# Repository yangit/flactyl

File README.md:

# Flactyl

## Contacts

If you need help building this keyboard or have any questions you can drop me a line at [yan@yan.my](mailto:yan@yan.my)

I'd be happy to help!

## Release notes

### 5.1

- Fix routes too close to mounting screw holes can be stripped if screw is overtightened

### 5.0

- PCBs v4 are not compatible with case v5, connector cutout location have been changed
- Moved thumb JST connector so that it is not necessary to trim JST cable
- Moved JST connectors, reset button, power switch on main PCBs such that it it easier make parametric case
- Added `.scad` for Iceberg/Clay cases

### 4.2

- First public release

## Features

- Thumb cluster with 6 keys, easy to use in combos, so ~12 combinations depending on how you setup combos
- 15g SPRiT springs to make same finger combos super easy
- Thumb cluster keys are designed to be poked with thumb nail/nose, not pressed with soft area, allows for easy access to all 6 keys with no wrist movement
- Multiple cases including the `clay` case to easily prototype your thumb cluster location
- Low distance between pinky and the table, allows to rest palms directly on the table without floating them, or using wrist rests.
- Heavy tenting at 60 degrees
- Kailh Choc V1 hotswap, with choc spacing
- Rotary encoder
- Ergogen for PCB with some custom scripts to generate `.bom` `.pos` files for jlcpcb.com SMT assembly service, and output outlines for easier 3d case designing
- zmk-config generator with custom NodeJS script to make layer declaration easier and more readable
- Nice!Nano positioned right under the keys, hiding itself, without need for manual wiring (because of that PCBs are non reversible)
- Can fit huge batteries
- Magnetic stripe to securely fasten to the table

## Videos and links

- Youtube video with detailed review is [here](https://www.youtube.com/watch?v=Pdhb9uNnzU0)
- Short [typing video](https://www.youtube.com/watch?v=eU5eg4PKMlQ)
- 3d models can be [interactively rotated](https://yangit.github.io/flactyl/)
- Video how to order 3d case from JLCPCB.com [here](https://www.youtube.com/watch?v=07qFKaykjfg)
- Video how to order PCBs from JLCPCB.com [here](https://youtu.be/oP7d0jU99oc)
- Reddit [thread](https://www.reddit.com/r/ErgoMechKeyboards/comments/13qep4y/after_4_year_lurking_and_2_years_building_my_own/)
- You can find [basic](https://github.com/yangit/zmk-config-flactyl/) zmk-config for this board and [my own config generator](https://github.com/yangit/zmk-config/)
- It took me two years to finish this project, thanks to [KBD.news](https://kbd.news/) for inspiration!

## Cases

There are 3 cases available:
**Clay**, **Iceberg**, **Hitam**  
3d models can be [interactively rotated](https://yangit.github.io/flactyl/)

### Clay

Consist of two pieces, you are supposed to put clay/play dough in it and see what position is best for you. It is pretty usable already.

### Iceberg

Consists of single hollow box, switches are exposed on the sides.

### Hitam

Pretty involved shape to cover all the keys from the sides as well.

## Customize case

You can customize thumb cluster location reasonably easy using
`./scad/` folder. Try to play around with it, you need OpenScad free software. Look for `./scad/readme.md` for more details.

## Build

High-level build steps looks like so:

- Select which case you want to print
- Order case and PCB from JLCPCB or any other pcb/3d printing vendor
- Order parts online from various vendors according to the parts list
- Solder
  - Pins on the Nice!Nanos themselves see [this](https://docs.splitkb.com/hc/en-us/articles/360011263059-How-do-I-socket-a-microcontroller-) guide
  - Headers for Nice!Nanos on the left and right PCBs
  - Hot-swap connectors for switches on all PCBs
  - Two switches above Nice!Nanos on each side of PCB (letters G,T,J,U on QUERTY)
  - Rotary encoders to PCBs
  - Batteries with connectors (only for wireless build)
- Assemble (do not worry, if you got this far it is only pure joy left)
  - Small tip, when screwing everything, you should use 2 nuts per screw, it goes like so
  - SCREW, WASHER, PCB, **NUT**, CASE, NUT. Notice the extra nut, it helps tremendously to fiddle all the screws through the case at the same time. See [here](./photos/parts/nut_how.jpg)
  - The JST connector will not fit into the thumb cluster side, that is fine, just trim it with a knife
- Flash it with ZMK firmware (or any other you want)
  - Spend months in agony migrating Querty => Workman => Colemak, moving around symbols, modifiers, and learning the intricate issues of how TAP-DANCE timings are implemented.
- Enjoy?
  - Enjoy!

Look up `Videos` section of this readme to see how to order PCBs and 3d files from JLCPCB.com

This is how PCB should come out from JLCPCB.com, complete with all diodes, JST connectors, power switch, reset button(not visible)

## Parts list

You are going to need some items to get done:

|  Count   | Name   | Photo   |
|-------------|-------------|-------------|
| 2 | EC11 Rotary encoder with a knob (ALP-ENC-TCT-001 or any similar will do), if you do not want to have a rotary encoder, you can just solder a normal switch in its place. It will work.| 
| 42 | Kailh Low Profile Choc V1 PG1350 switches (highly recommend getting 20g (pink) for thumb cluster to make multi key combos easier)|  
| 42 | 1u Blank MBK Choc Low Profile Keycaps| 
| 2 | Pitch 2.54mm 1 * 40 Pin Sets of headers/sockets for Nice!Nanos| 
| 2 | Nice!Nano micro controllers| 
| 2 | Mill Max 3320 Pins for Nice!Nano micro controllers, they are soldered to your Nice!Nanos, and that allows you to plug nice nano into headers, buy default Nice!Nanos come with square pins not suitable for socketing (see photos), the default ones can only be used to permanently solder controller onto the PCB **which should be avoided**. If the pins are expensive or unavailable you can buy any through hole diodes and cut their legs to use instead, though legs are thinner and are slightly harder to work with, see [this](https://docs.splitkb.com/hc/en-us/articles/360011263059-How-do-I-socket-a-microcontroller-) guide|    
| 32 | Hot swap connectors for PG1350 | 
| 2 | Case|
| 4 | Pcb (one for each half and two for thumb clusters)|  
| 12 | M2 x 10mm Screws (I recommend getting hex head screws, they are easier to tighten)| 
| 12 | M2x3x3x1.8 square (!NOT regular hex!) nuts, see photo|
| 12 | Spring washers |
| 2 | JST SH 1.0mm x 2 wires x 100mm long wire connector for battery (only if you want to go wireless)| 
| 2 | Battery, any single cell Li-ion/Li-po 100-1000mah will do, connector does not matter, you going to resolder it anyway  (only if you want to go wireless)| 
| 2 | JST SH 1.0mm x 5 wire x 100mm long cable for thumb cluster (carefully look at the cable colors, there are two types of connector with  cross over and direct, you need connector with the same color order on both sides ), second photo shows how you will need to trim the connector using utility knife to make sure it fits into the pcb| 
| 8 | 8mm silicone rubber feet (self adhesive)| 
| 1 | Roll of 3m magnetic strip 1inch wide (25.4mm) for the undercase holder. Unless your table is metal you need to glue the other part of the tape on the table as well like on the photo => |   
|2|USB-C cables of your preference, one will connect your main half and computer to communicate keypresses and provide power, another between your driven half and any power source, to provide power only. You may not need 2 cables and get away with one USB-C cable if you intend to use battery, also 2 cables are handy when you need to re-flash your controllers with new firmware|

You will also need

- Screw driver
- Soldering iron with flux and solder
- Knife to trim JST connectors for thumb cluster

## ZMK-config

You can take a basic config for this shield [here](https://github.com/yangit/zmk-config-flactyl/)

## Structure of this repo

### `./production`

You can grab `.zip` and `.stl` here, and send them to JLCPCB.com, they will print case, and PCB, it also includes BOM and POS files so that JLCPCB can solder connectors, diodes, reset button and power switch on the board for you.

Look up `Videos` section of this readme to see how to order PCBs and 3d files from JLCPCB.com

### `./ergogen`

YOU DO NOT NEED THIS

unless you want to mess with my PCB generation code, you can just grab readymade pcb from `./production/`
Modified fork of [ergogen](https://github.com/ergogen/ergogen) now can be found [here](https://github.com/yangit/ergogen)

This folder will appear to be empty if you try to `git clone` or download a zip archive, you just need to run

```bash
git clone https://github.com/yangit/flactyl
cd ./flactyl
git submodule init
git submodule update
```

Now your `./ergogen` should contain latest code.
Alternatively you can proceed to [here](https://github.com/yangit/ergogen) to find contents of `./ergogen` folder.

To build it make sure you have npm/nodejs installed:

```bash
cd ./ergogen
npm install
./input/bulid.sh
```

This will produce files in the `./ergogen/output` folder.
Now you need to prepare them for JLCPCB, you HAVE to follow requirements in `./ergogen/input/readme.md`, notice that it is in subfolder `./input` and not the root level `readme.md`

 and they can be used for JLCPCB.com printing, that includes `.pos` and `.bom` files for SMT assembly.
If you are looking to make any changes, go under `./ergogen/input` folder and change config files there.

## Photos

## What I have learned

### 3d printing materials (From JLCPCB.com)

- ABS plastic, the surface finish is not there. It should be painted or it is too rough. I do not like the resolution of the ABS FDM
- SLA (resin) `LEDO 6060`: the plastic is very nice, white, finish is great, but it will [yellow significantly](./photos/parts/yellowing.jpg) if you expose it to the sunlight, my keyboard looks like that after 2 months on my desk and some direct summer sun. Notice how the inside did not yellow.
- SLA (resin) `Black Resin`: it is very dark grey, satin, finish is very smooth, I like it.

### 3d design

If you are a programmer:

Do not try to design anything in Fusion 360, it is way too easy, visual, and you have so many tools at your disposal. Until one day you need to refactor your model and add a minor change somewhere in the past.
Screw Fusion 360! It will mess up your model in this case no matter how hard you try to make your model parametric and no matter how careful you are taking care of your history.

GIT + OpenScad is 100% more predictable, you might need to write your own helpers, but it was 10 times faster than fiddling with Fusion 360.

### Config generator

Also you will most likely need your own ZMK/QMK config generator. Basic layers, are ok to write by hand, but tap dances are just horrible in both ZMK and QMK, my config generator of ~500 lines in JavaScript generates `.keymap`  ~5000 lines long. How am I supposed to maintain it manually? Features I have in my generator are:

- mirror layer
- create layer from another, but with modifier
- easily define macros, tap-dance etc
- fix tap-dance timing mess

You can take a look at my config generator [here](https://github.com/yangit/zmk-config/)

### Mirror layers

I use split in programs like Photoshop and Fusion 360. One of the problems I had is when you need to press single hotkey i.e. letter “L” which is on the right side. Moving my hand from the mouse for that single press is simply annoying.

So I had these solutions:

#### Fusion 360 layer

I would enable it when I navigate to fusion and all most common keys would be on the left hand. I.e. I would put “L” under right index. That allows me to comfortably use any program and all wired shortcuts like “CMD+CTRL+X+P+F2+NUM14” BUT! If I need to switch back and forth between fusion and gmail, or if I need to label objects in my model (type short stings of text) it becomes a pain to switch to/from the layer unless it is a momentary layer. Overall it is a very quick/easy solution, and if you have stable workflow(know your hotkeys) and there are not too many programs(and so layers) you can get away with it.

#### Mirror layer

On my left half i have a “mirror” layer which swaps all the letters from the right half. Using that magic button I can all of a sudden type any key any time with one hand. So great! Gmail hotkeys, chrome, photoshop, fusion all of them work w/o custom layers and on one hand.
BUT then you realize that you not only need letter L but also CMD+L or SHIFT+CMD+L and that is still manageable by using “tap dance” Essentially short tap emits “L”, hold emits “CMD+L” and tap and hold emits “CMD+SHIFT+L” Ok good? Not yet, there are more than letters you want to mirror, sometimes you need to type single “!” Or just press that “up” key once, or else. So I ended up using 3 mirror layers.

- letters
- symbols
- arrows (it also has stuff like PageUp etc)

Then there is an issue. You need to be able to activate all 8 layers from one hand:

- letters
- mirror letters
- symbols
- mirror symbols
- arrows
- mirror arrows
- shift layer
- mirror shift layer

Ok, we need to talk here. Lets drop the last two, that brings number to 6. The first one(letters) you do not need to activate it is already active. Now you need to increase number of layers you can comfortably activate on the left hand. One approach is to press thumb on two keys simultaneously. If your thumb cluster looks like so {a, b, c} you can press “a”, “b”, “c“ but also “ab” and “bc”. You have got 5 layers instead of 3. That depends on your thumb cluster and that is why I do not like splay(rotation) on thumb keys. I like them aligned next to each other like on [moonlander](https://www.zsa.io/moonlander/) keyboard. Having easy 20g spring under thumb keys helps a lot with pressing two keys simultaneously.

#### Integrate mouse into keyboard

I’m still on the way to this solution, but if you get like [Charybdis](https://bastardkb.com/charybdis/) you may be happy since your hands are not leaving keyboard at all.

## Mods

- If 20g pink Choc are unavailable you can do 15g SPRiT springs mod, it is tedious, but worth it if all you got is 40g linear.
- Ball bearing mod: somehow ball bearing mod did not work as well on Kailh Choc as it did on Kailh Box, so I can not recommend it to reduce travel, I was able to add balls, but the slightly reduced travel immediately affected the consistency and I had to type harder or twice to get key to fire.

## License

MIT

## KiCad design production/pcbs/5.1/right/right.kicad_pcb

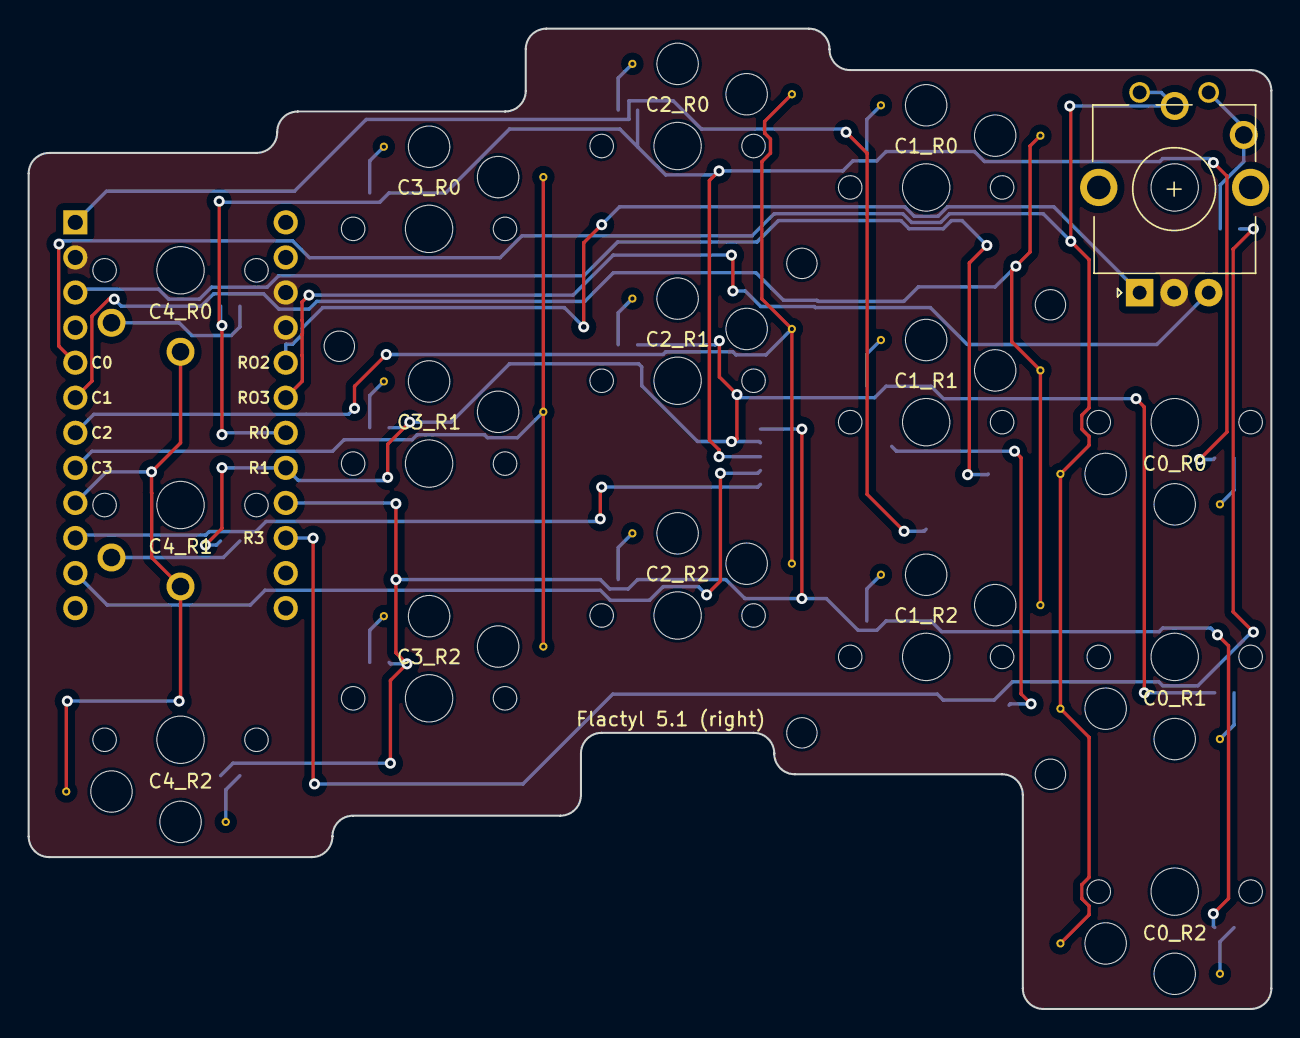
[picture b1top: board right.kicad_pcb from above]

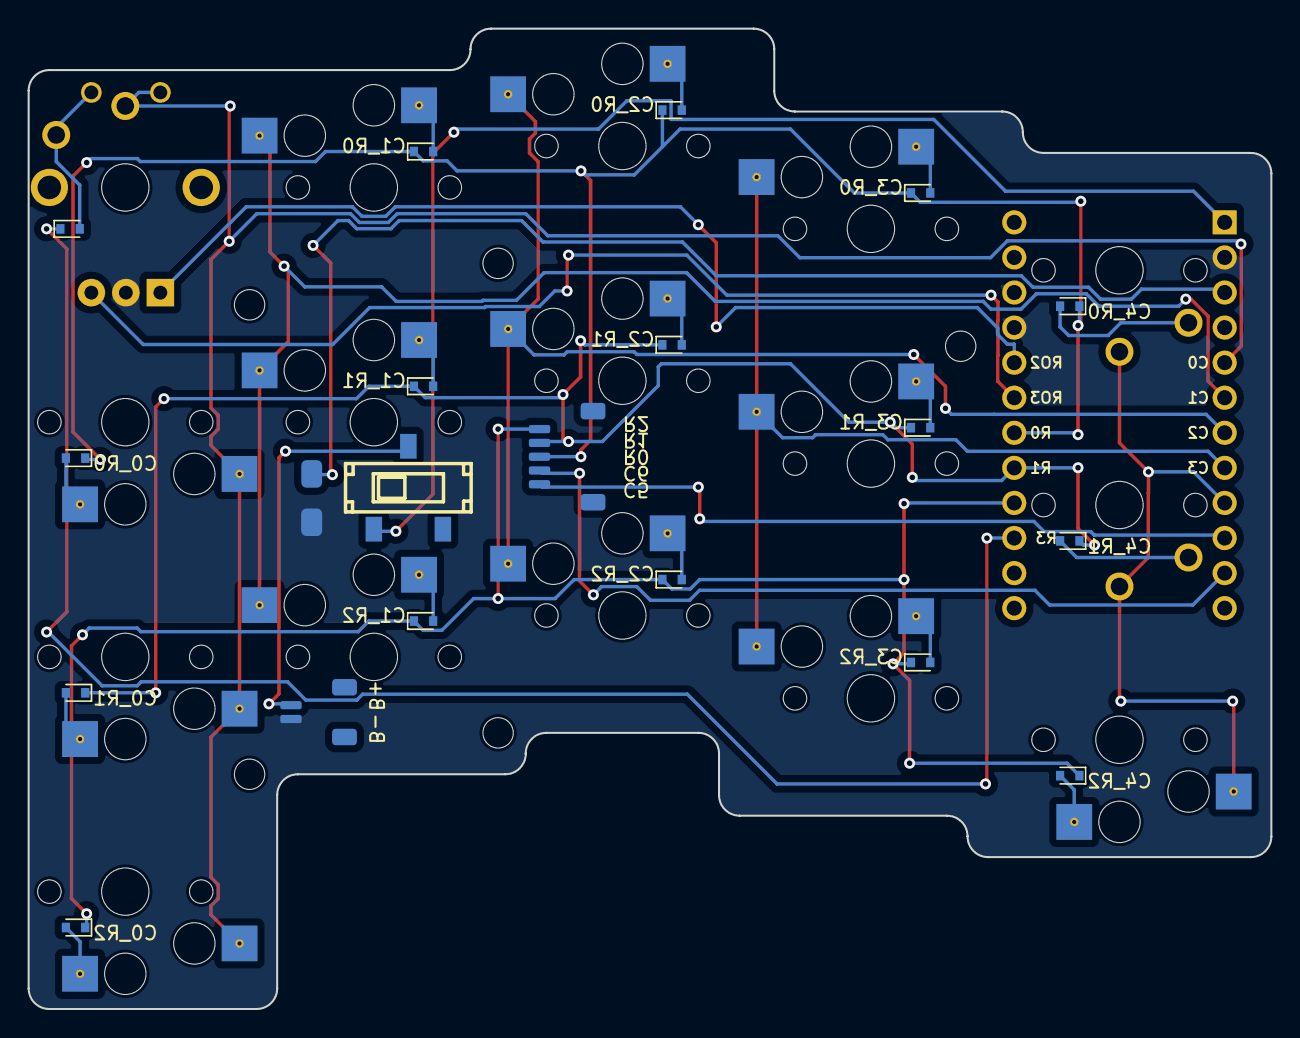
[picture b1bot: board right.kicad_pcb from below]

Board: 2 copper layers, 90.0 x 71.0 mm, 43 parts (36 on the bottom side), 33 nets.

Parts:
D1, D2, D3, D4, D5, D6, D7, D8, D9, D10, D11, D12, D13, D14, D15, D16: D_SOD-523
H1, H2, H3, H4, H5: MountingHole_2.2mm_M2
JB1: JST_SH_SM02B-SRSS-TB_1x02-1MP_P1.00mm_Horizontal
JC1: JST_SH_SM05B-SRSS-TB_1x05-1MP_P1.00mm_Horizontal
MCU1: NiceNano
ROT1: rotary_encoder
S1, S2, S3, S4, S5, S6, S7, S8, S9, S10, S11, S12, S13, S14, S15: Kailh_socket_PG1350_no_silk
SB1: b3u-1000P
SS1: SW-SMD_SS-3235D-03-L2.00
T1: Flactyl 5.1 (right); somelogo

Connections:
BSLI: JB1.2, SS1.2
C0: MCU1.5, ROT1.1, ROT1.2, S3.2, S3.4, S4.2, S4.4, S5.2, S5.4
C0_R0D: D4.2, S3.1, S3.3
C0_R1D: D5.2, S4.1, S4.3
C0_R2D: D6.2, S5.1, S5.3
C0_R3D: D3.2, ROT1.1, ROT1.2
C1: MCU1.6, S6.2, S6.4, S7.2, S7.4, S8.2, S8.4
C1_R0D: D7.2, S6.1, S6.3
C1_R1D: D8.2, S7.1, S7.3
C1_R2D: D9.2, S8.1, S8.3
C2: MCU1.7, S9.2, S9.4, S10.2, S10.4, S11.2, S11.4
C2_R0D: D10.2, S9.1, S9.3
C2_R1D: D11.2, S10.1, S10.3
C2_R2D: D12.2, S11.1, S11.3
C3: MCU1.8, S12.2, S12.4, S13.2, S13.4, S14.2, S14.4
C3_R0D: D13.2, S12.1, S12.3
C3_R1D: D14.2, S13.1, S13.3
C3_R2D: D15.2, S14.1, S14.3
C4: MCU1.9, S1.2, S2.2, S15.2, S15.4
C4_R0D: D1.2, S1.1
C4_R1D: D2.2, S2.1
C4_R2D: D16.2, S15.1, S15.3
C5: JC1.1, MCU1.10
C6: JC1.2, MCU1.11
GND: JB1.1, MCU1.2, MCU1.15, MCU1.16, ROT1.C, SB1.1
P2: MCU1.17, ROT1.A
P3: MCU1.18, ROT1.B
R0: D1.1, D4.1, D7.1, D10.1, D13.1, JC1.3, MCU1.19
R1: D2.1, D5.1, D8.1, D11.1, D14.1, JC1.4, MCU1.20
R2: D6.1, D9.1, D12.1, D15.1, D16.1, JC1.5, MCU1.21
R3: D3.1, MCU1.22
RAW: MCU1.1, SS1.1
RST: MCU1.3, SB1.2

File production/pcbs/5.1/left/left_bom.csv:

Comment,Designator,Footprint,LCSC
"DIODE","D1,D2,D3,D4,D5,D6,D7,D8,D9,D10,D11,D12,D13,D14,D15,D16","Yan:D_SOD-523","C511874"
"JC","JC1","Yan:JST_SH_SM05B-SRSS-TB_1x05-1MP_P1.00mm_Horizontal","C136657"
"JB","JB1","Yan:JST_SH_SM02B-SRSS-TB_1x02-1MP_P1.00mm_Horizontal","C160402"
"SB","SB1","Yan:b3u-1000P","C231329"
"SS","SS1","Yan:Slide switch","C381097"

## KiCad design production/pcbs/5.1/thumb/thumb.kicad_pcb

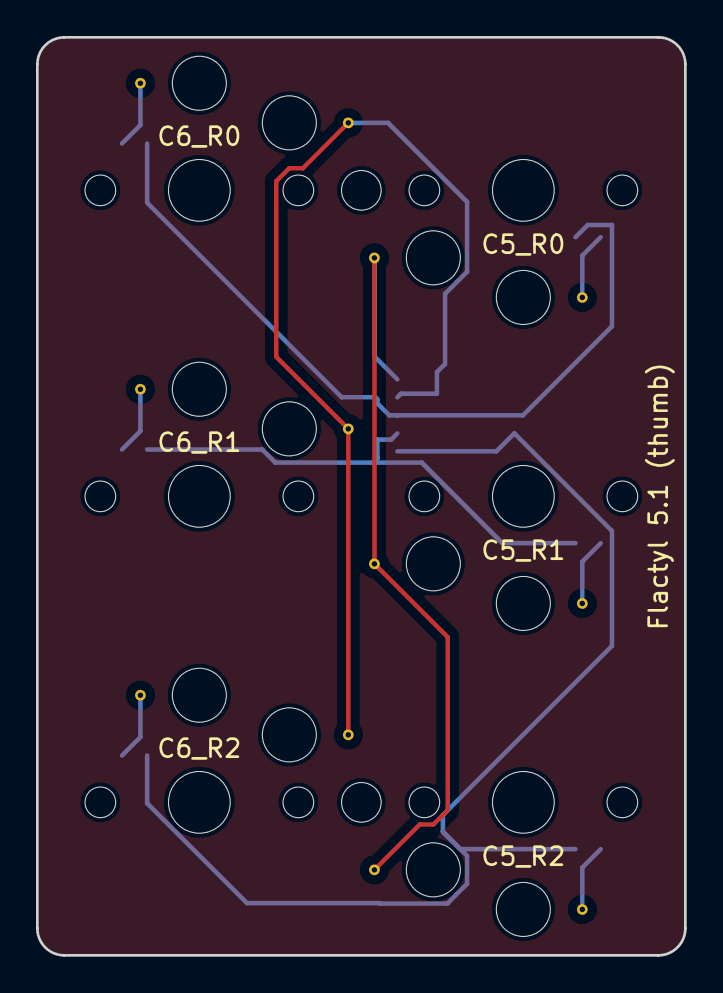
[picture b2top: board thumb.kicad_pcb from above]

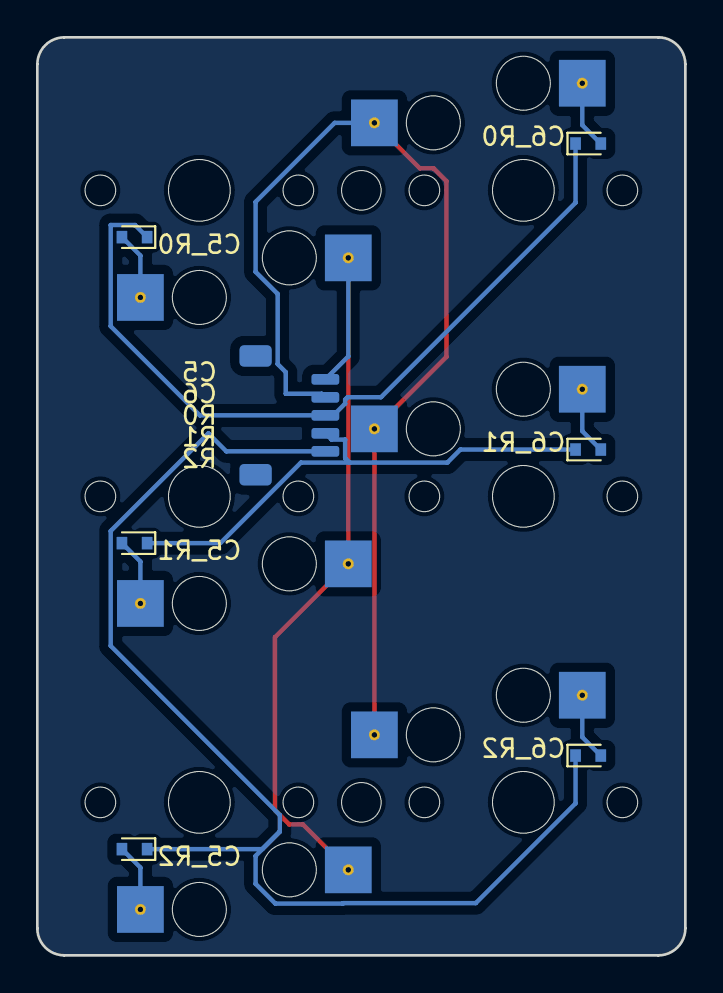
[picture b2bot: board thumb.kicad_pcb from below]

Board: 2 copper layers, 36.0 x 51.0 mm, 18 parts (13 on the bottom side), 11 nets.

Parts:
D1, D2, D3, D4, D5, D6: D_SOD-523
H1, H2: MountingHole_2.2mm_M2
JC1: JST_SH_SM05B-SRSS-TB_1x05-1MP_P1.00mm_Horizontal
S1, S2, S3, S4, S5, S6: Kailh_socket_PG1350_no_silk
T1: Flactyl 5.1 (thumb); somelogo
T2: x; somelogo
T3: y; somelogo

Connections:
C5: JC1.1, S1.2, S1.4, S2.2, S2.4, S3.2, S3.4
C5_R0D: D1.2, S1.1, S1.3
C5_R1D: D2.2, S2.1, S2.3
C5_R2D: D3.2, S3.1, S3.3
C6: JC1.2, S4.2, S4.4, S5.2, S5.4, S6.2, S6.4
C6_R0D: D4.2, S4.1, S4.3
C6_R1D: D5.2, S5.1, S5.3
C6_R2D: D6.2, S6.1, S6.3
R0: D1.1, D4.1, JC1.3
R1: D2.1, D5.1, JC1.4
R2: D3.1, D6.1, JC1.5

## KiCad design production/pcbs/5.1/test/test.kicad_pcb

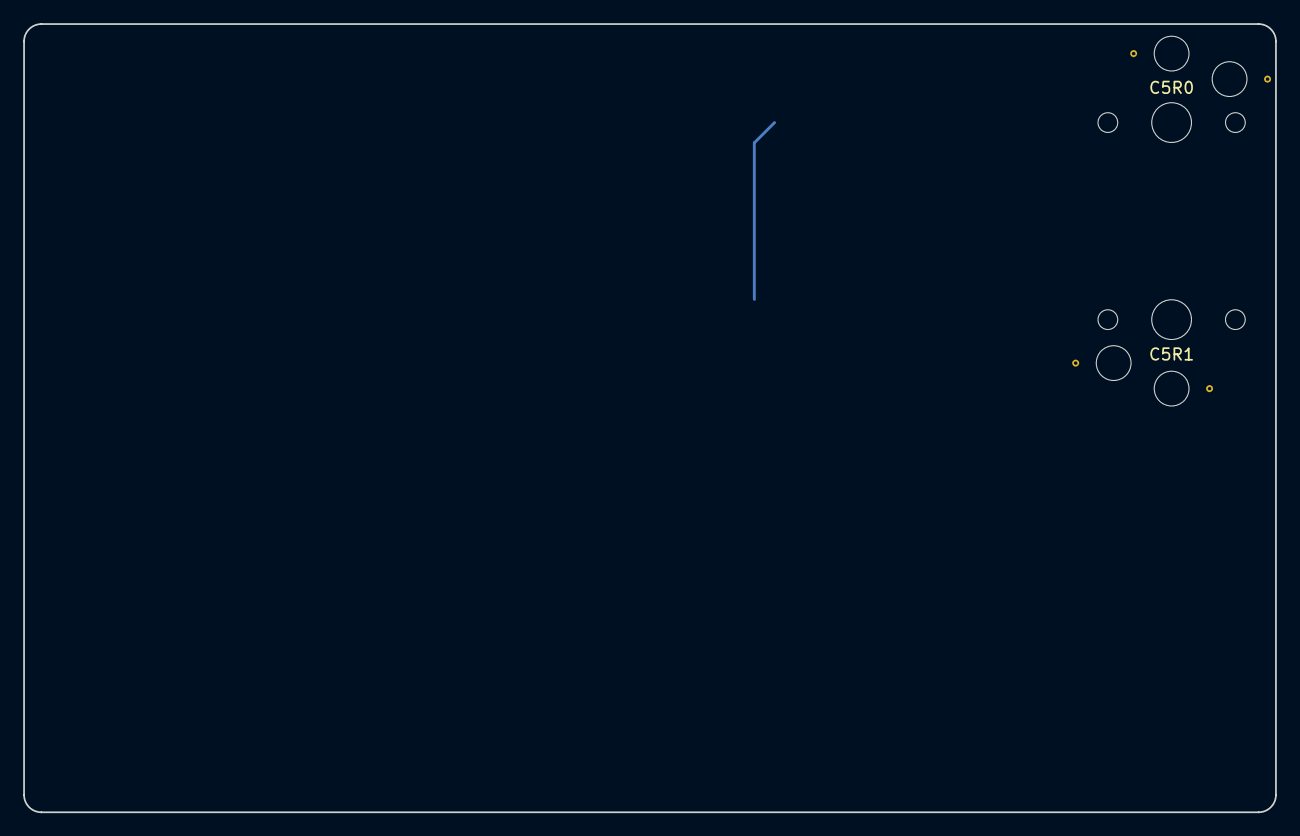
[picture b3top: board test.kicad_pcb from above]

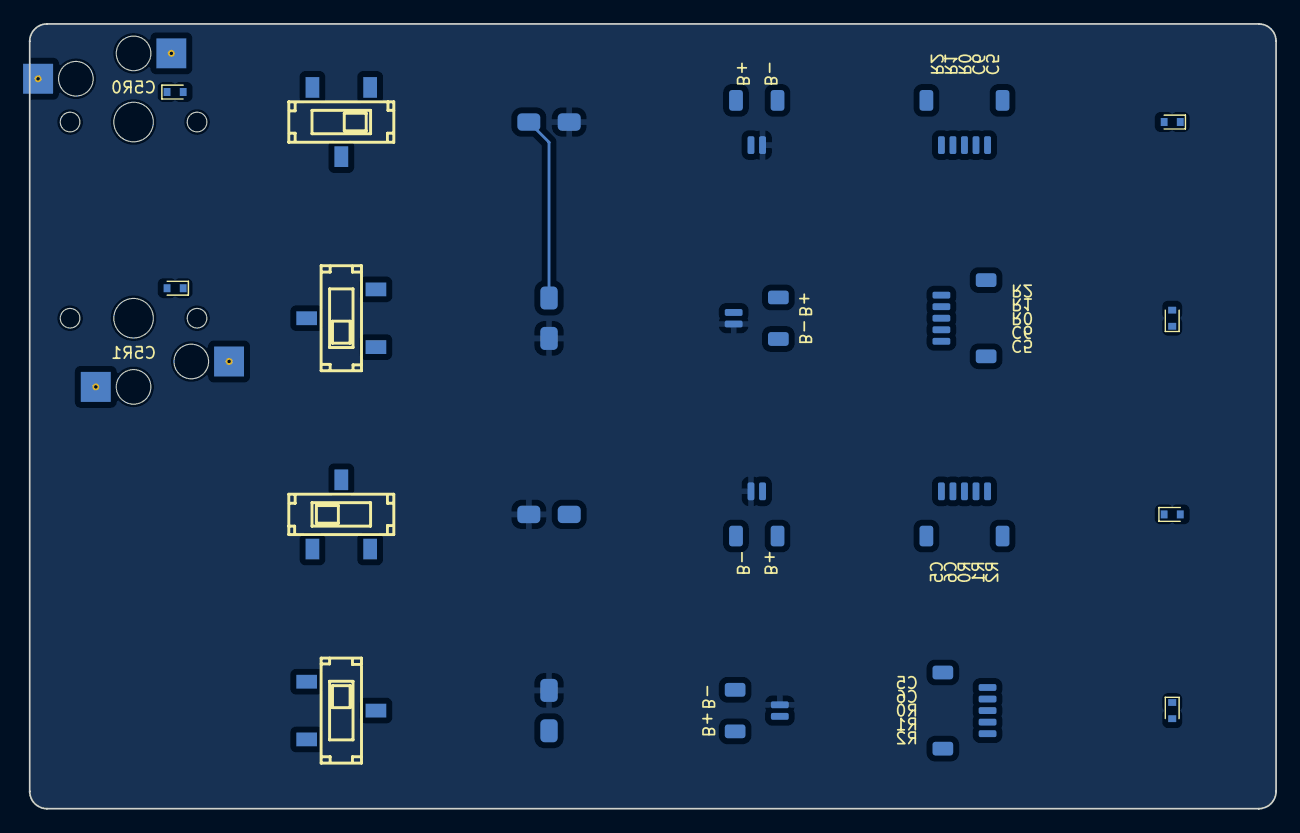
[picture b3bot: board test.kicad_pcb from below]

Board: 2 copper layers, 108.0 x 68.0 mm, 26 parts (24 on the bottom side), 14 nets.

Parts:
D1, D2, D3, D4, D5, D6: D_SOD-523
JB1, JB2, JB3, JB4: JST_SH_SM02B-SRSS-TB_1x02-1MP_P1.00mm_Horizontal
JC1, JC2, JC3, JC4: JST_SH_SM05B-SRSS-TB_1x05-1MP_P1.00mm_Horizontal
S1, S2: Kailh_socket_PG1350_no_silk
SB1, SB2, SB3, SB4: b3u-1000P
SS1, SS2, SS3, SS4: SW-SMD_SS-3235D-03-L2.00
T1: x; somelogo
T2: y; somelogo

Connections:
BSLI: JB1.2, JB2.2, JB3.2, JB4.2, SS1.2, SS2.2, SS3.2, SS4.2
C5: JC1.1, JC2.1, JC3.1, JC4.1, S1.2, S1.4, S2.2, S2.4
C5R0D: D5.2, S1.1, S1.3
C5R1D: D6.2, S2.1, S2.3
C6: JC1.2, JC2.2, JC3.2, JC4.2
GND: JB1.1, JB2.1, JB3.1, JB4.1, SB1.1, SB2.1, SB3.1, SB4.1
R0: D5.1, JC1.3, JC2.3, JC3.3, JC4.3
R1: D6.1, JC1.4, JC2.4, JC3.4, JC4.4
R2: JC1.5, JC2.5, JC3.5, JC4.5
RAW: SS1.1, SS2.1, SS3.1, SS4.1
RST: SB1.2, SB2.2, SB3.2, SB4.2
f: D1.2, D2.2, D3.2, D4.2
t: D1.1, D2.1, D3.1, D4.1
three: SS1.3, SS2.3, SS3.3

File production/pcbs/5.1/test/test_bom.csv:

Comment,Designator,Footprint,LCSC
"DIODE","D1,D2,D3,D4,D5,D6","Yan:D_SOD-523","C511874"
"JC","JC1,JC2,JC3,JC4","Yan:JST_SH_SM05B-SRSS-TB_1x05-1MP_P1.00mm_Horizontal","C136657"
"JB","JB1,JB2,JB3,JB4","Yan:JST_SH_SM02B-SRSS-TB_1x02-1MP_P1.00mm_Horizontal","C160402"
"SB","SB1,SB2,SB3,SB4","Yan:b3u-1000P","C231329"
"SS","SS1,SS2,SS3,SS4","Yan:Slide switch","C381097"

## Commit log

2023-05-24 Init
2023-05-24 gitignore
2023-05-24 Reddit link
2023-05-24 Short typing video
2023-06-01 More openscad
2023-06-02 Add much stuff to case
2023-06-02 keycap cut
2023-06-02 more chaneges
2023-06-02 export .stl
2023-06-05 More scad
2023-06-06 push function API
2023-06-06 Screws in place
2023-06-06 Hollow case
2023-06-06 Case is mostly stable
2023-06-06 cutouts for switches
2023-06-06 Minor fix
2023-06-06 Small fixes
2023-06-06 Extend case keywell beyond keys
2023-06-07 edge fixes
2023-06-08 move files
2023-06-08 Move stuff around
2023-06-08 Photos and instructions.
2023-06-08 Submodule
2023-06-08 typo
2023-06-08 Readme
2023-06-08 Add iceberg stl and photos
2023-06-08 Add more photos and cases
2023-06-08 Redme
2023-06-08 How to 3d case
2023-06-08 Tape photo
2023-06-08 Update ref
2023-06-08 update submodule
2023-06-08 Pull ergogen
2023-06-09 Add box API
2023-06-09 Refactor scad
2023-06-09 Add clay scad for thumb
2023-06-09 More utility functions
2023-06-09 Add clay .scad
2023-06-09 Clay case
2023-06-12 Fix readme
2023-06-13 Mill max pins description
2023-06-13 More pins
2023-06-13 Stl for clay
    Clay .stl
    Readme and others
    Remove undone
    Fixes
    Wip iceberg
    Iceberg
2023-06-13 fixes
2023-06-13 mods
2023-06-13 Clay and image generation
2023-06-13 Generated images for clay and iceberg
2023-06-13 keycaps rounded
2023-06-13 iceberg variants
2023-06-13 ergogen
2023-06-13 Move slider and reset buttons
2023-06-14 Files
2023-06-14 sider
2023-06-14 Rotary to switch
2023-06-15 Add ergogen
2023-06-15 Move pcbs
2023-06-15 routed left 5.0
2023-06-15 V5 pcbs
2023-06-15 Export Iceberg v5
2023-06-16 Versions
2023-06-16 Add right pcb
2023-06-16 mill max pin number
2023-06-20 Fix case 4.2
2023-06-20 add text version
2023-06-20 Case rebuild
2023-06-20 Add case names
2023-06-27 photos
2023-06-27 photo update
2023-06-29 ergogen and thumb3 increase thumb hole size
2023-06-29 fix cufout position
2023-06-29 USB cutout
2023-06-29 yellowing
2023-06-29 HItam work start
2023-06-29 iceberg-ploopy
2023-06-29 rm submodule
2023-06-30 Cirque connector pcb
2023-06-30 Some more connectors.
2023-06-30 Hitam case
2023-06-30 hitam
2023-07-01 build fixes
2023-07-01 legs and magnet holder
2023-07-02 generated keys
2023-07-02 assymetric thumb holes
2023-07-02 hitam automation
2023-07-02 Rebuild
2023-07-02 Cleanup and fixes
2023-07-02 Version
2023-07-02 move build
2023-07-02 docs
2023-07-02 docs2
2023-07-02 docs3
2023-07-02 docs5
2023-07-02 docs4
2023-07-04 Deploy docs
2023-07-04 js keys
2023-07-04 .ojb
2023-07-04 add obj
2023-07-05 .gltf
2023-08-01 PCB 5.1
